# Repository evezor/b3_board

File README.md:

# b3_board
*please note this board is now depricated

The B3 board was meant as a test board to test the Edge networking and to test the fit with the edge stamp board. 

There are a couple leds, buttons, a potentiometer and connections for the canbus. 

Evezor and all associated marks, logos, and designs are registered trademarks and protected by copyright. Unauthorized use or reproduction of these trademarks and copyrighted materials is strictly prohibited

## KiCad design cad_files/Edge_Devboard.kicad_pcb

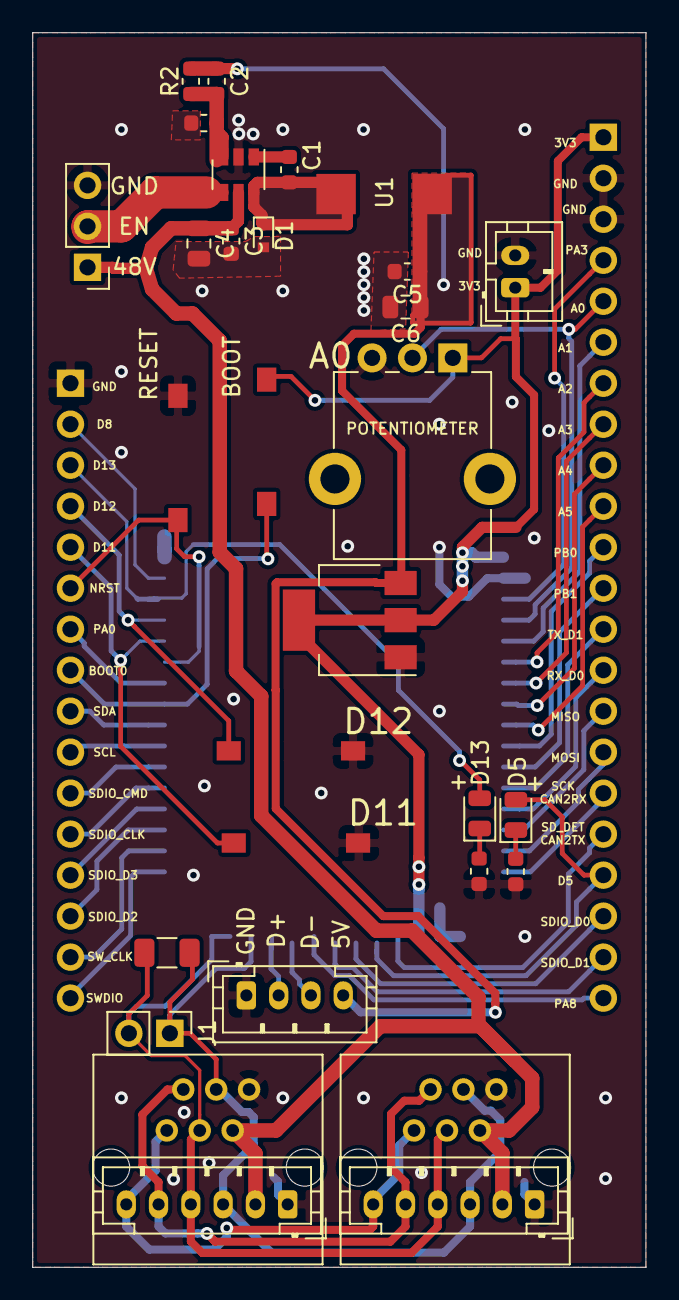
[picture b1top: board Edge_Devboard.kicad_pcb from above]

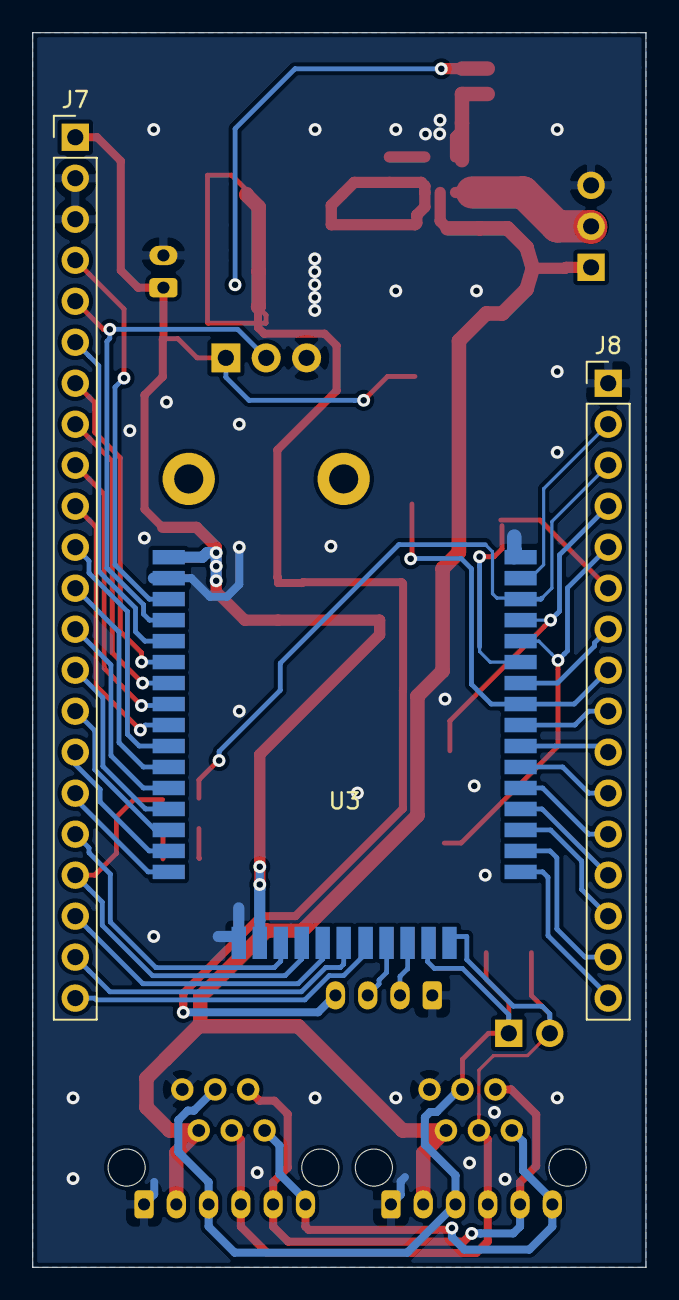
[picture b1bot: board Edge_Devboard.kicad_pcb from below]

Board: 2 copper layers, 38.0 x 76.5 mm, 33 parts (3 on the bottom side), 50 nets.

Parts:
C1, C2, C3, C5: .1uF; C_0603_1608Metric
C4: 4.7uF; C_0805_2012Metric
C6: 22uF; C_0805_2012Metric
D1: D_Schottky; D_SOD-523
D2, D3: LED; LED_0805_2012Metric
J1: Conn_01x02; PinHeader_1x02_P2.54mm_Vertical
J2, J3: RJ11; RJ11_C189747_Horizontal
J4, J5: PH; JST_PH_B6B-PH-K_1x06_P2.00mm_Vertical
J6: Conn_01x03; PinHeader_1x03_P2.54mm_Vertical
J7: Conn_01x22; PinHeader_1x22_P2.54mm_Vertical
J8: Conn_01x16; PinHeader_1x16_P2.54mm_Vertical
J9: Conn_01x04; JST_PH_B4B-PH-K_1x04_P2.00mm_Vertical
J10: Conn_01x02; JST_PH_B2B-PH-K_1x02_P2.00mm_Vertical
L1: 22uH; INDUCTOR_22uH_GCDA0650-220MC
R1, R4, R5: 15k; R_0603_1608Metric
R2: 82k; R_0603_1608Metric
R3: 120; R_1206_3216Metric
RV1: R_POT; Potentiometer_Alpha_RD901F-40-00D_Single_Vertical_CircularH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
SW1: RESET; SWITCH_2x3_SMD_TACTILE_GREEN
SW2: BOOT; SWITCH_2x3_SMD_TACTILE_GREEN
SW3: D12; SWITCH_2x3_SMD_TACTILE_GREEN
SW4: D11; SWITCH_2x3_SMD_TACTILE_GREEN
U1: V_REG; SOT-23-6
U2: AMS1117-3.3; SOT-223-3_TabPin2
U3: EDGE_STAMP

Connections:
+3V3: J7.1, J10.1, RV1.1, SW2.2, U2.2, U3.1, U3.18
+48V: C3.1, C4.1, J2.2, J3.2, J4.2, J5.2, J6.1, U1.5
/5V: C2.1, C5.1, C6.1, J9.4, L1.2, R2.1, U2.3
/CAN_H: J1.1, J2.3, J3.3, J4.3, J5.3, R3.2, U3.26
/CAN_L: J1.2, J2.4, J3.4, J4.4, J5.4, R3.1, U3.27
/EN: J6.2, U1.4
/FD_H: J2.5, J3.5, J4.5, J5.5
/FD_L: J2.6, J3.6, J4.6, J5.6
GND: C3.2, C4.2, C5.2, C6.2, D1.2, J2.1, J3.1, J4.1, J5.1, J6.3, J7.2, J7.3, J8.1, J9.1, J10.2, R1.1, R4.1, R5.1, RV1.3, SW1.2, SW3.2, SW4.2, U1.2, U2.1, U3.2, U3.17, U3.43
unnamed: C1.1, D1.1, L1.1, U1.6
unnamed: C1.2, U1.1
unnamed: C2.2, R1.2, R2.2, U1.3
unnamed: D2.1, R4.2
unnamed: D2.2, J7.19, U3.20
unnamed: D3.1, R5.2
unnamed: D3.2, J8.3, U3.41
unnamed: J7.4, U3.3
unnamed: J7.5, RV1.2, U3.4
unnamed: J7.6, U3.5
unnamed: J7.7, U3.6
unnamed: J7.8, U3.7
unnamed: J7.9, U3.8
unnamed: J7.10, U3.9
unnamed: J7.11, U3.10
unnamed: J7.12, U3.11
unnamed: J7.13, U3.12
unnamed: J7.14, U3.13
unnamed: J7.15, U3.14
unnamed: J7.16, U3.15
unnamed: J7.17, U3.16
unnamed: J7.18, U3.19
unnamed: J7.20, U3.21
unnamed: J7.21, U3.22
unnamed: J7.22, U3.23
unnamed: J8.2, U3.42
unnamed: J8.4, SW3.1, U3.40
unnamed: J8.5, SW4.1, U3.39
unnamed: J8.6, SW1.1, U3.38
unnamed: J8.7, U3.37
unnamed: J8.8, SW2.1, U3.36
unnamed: J8.9, U3.35
unnamed: J8.10, U3.34
unnamed: J8.11, U3.33
unnamed: J8.12, U3.32
unnamed: J8.13, U3.31
unnamed: J8.14, U3.30
unnamed: J8.15, U3.29
unnamed: J8.16, U3.28
unnamed: J9.2, U3.25
unnamed: J9.3, U3.24

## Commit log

2023-09-10 add pics
2023-09-10 Create LICENCE
